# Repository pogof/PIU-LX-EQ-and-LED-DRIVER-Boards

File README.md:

Before you continue reading:
Both boards are relatively simple, both based on AtMega238p
and both running the same code. Both original board types
have the chip unlocked, meaning that with some programmer
or even just Arduino running the Example programmer sketch
you can read the code and flash it to another.

If you have a board that died you can first try to revive it
by flashing code downloaded from a working board. If that doesn't
work, try checking for component failure (caps shorted, ...),
replace the AtMega238p and flash again.

Please be careful, I am not responsible if you accidentally
damage, wipe or owerwrite your working boards!!!

If you are missing a board or want to make more continue reading.

## WHAT IS THIS?

In this archive you will find two KiCad 10 projects + all footprint
and symbol libraries. One project has the main EQ board and the other
the 3 light boards that are chained to the EQ board.

The connections were just traced by eye and multimeter.

The included schematics map out all the components as found on the original
boards. There are links to manufacturers websites of the connectors.

The PCB design should really only be used as a reference. The size
and mounting hole spacing has been checked and is correct. Component
layout is approximately the same as on the original board,
but the passives have whatever footprint I found, same as the dipswitch
and some other components. Basically if you want to make it,
make sure you change the footprints on the board to
what is actually available.

**PLEASE NOTE THAT YOU WILL NEED AT LEAST ONE OF THE ORIGINAL BOARDS
AND AT LEAST AN ARDUINO TO GET THE CODE OFF OF THE ORIGINAL BOARD.
I do not and will not share so i don't get in troubles.
This archive was made just for preservation purposes.**

# Other then the 2pin and 4pin power connectors, the footprint connectors are correct.

For the mini-fit: The footprint I have selected and the actual component I bought are slightly different, where the footprint is slightly rectangular, but the actual component I bought is square. I am not sure if there is different SKUs that differ or if it is straight up different connectors. Will update when I investigate some more.

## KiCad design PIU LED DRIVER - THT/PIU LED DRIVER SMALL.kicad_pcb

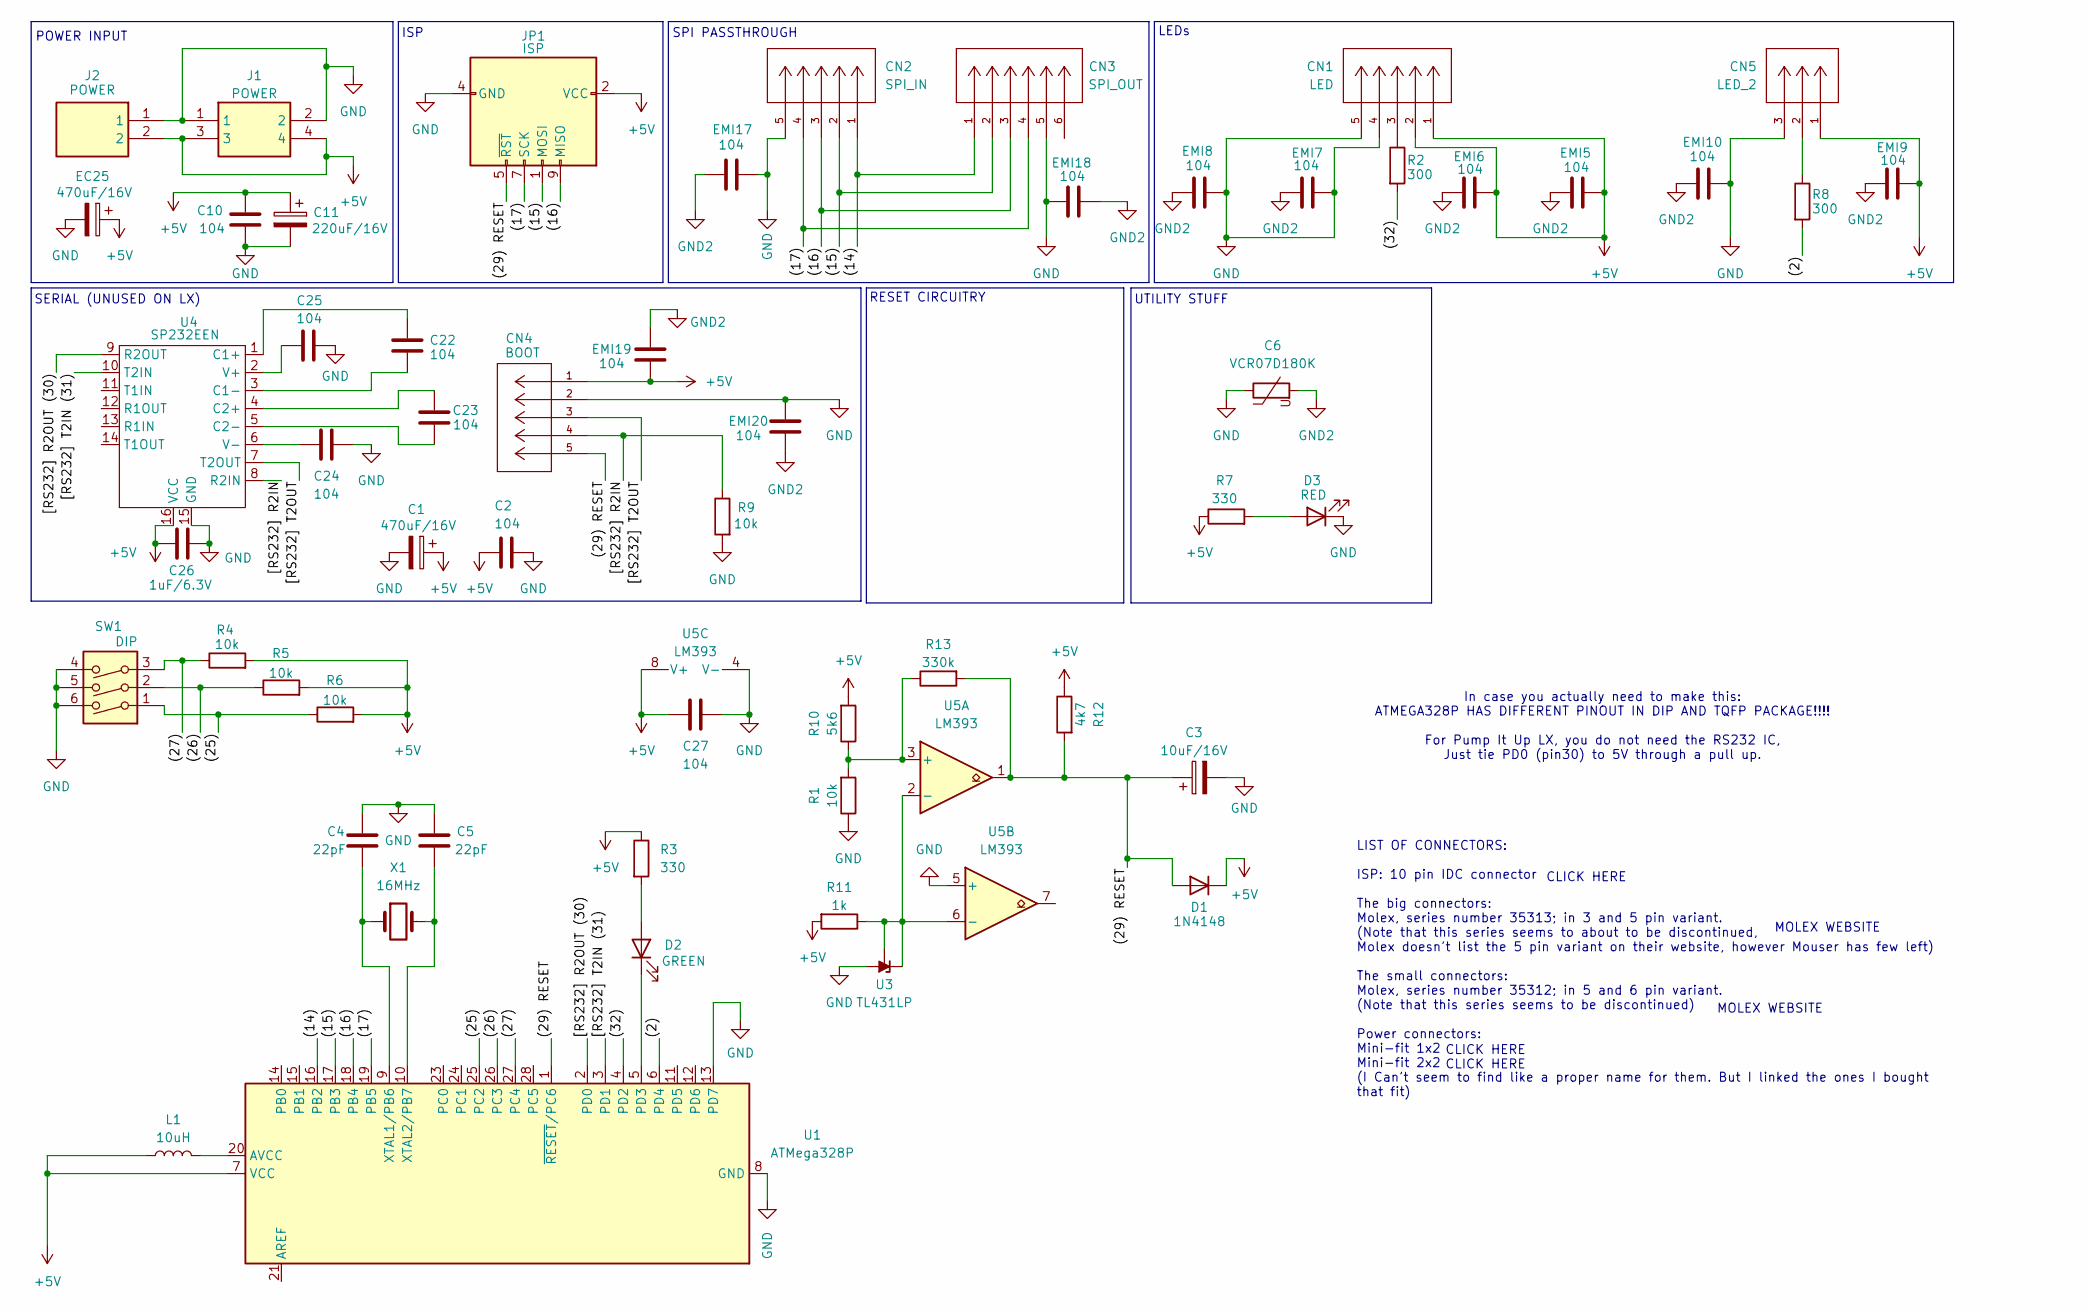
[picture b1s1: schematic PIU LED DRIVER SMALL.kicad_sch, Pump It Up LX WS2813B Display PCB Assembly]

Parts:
C1: 470uF/16V; CP_Radial_D8.0mm_P5.00mm
C2, C10, C22, C23, C24, C25, C27: 104; C_Disc_D6.0mm_W2.5mm_P5.00mm
C3: 10uF/16V; CP_Radial_D4.0mm_P2.00mm
C4, C5: 22pF; C_Disc_D3.8mm_W2.6mm_P2.50mm
C6: VCR07D180K; C_Disc_D6.0mm_W2.5mm_P5.00mm
C11: 220uF/16V; CP_Radial_D6.3mm_P2.50mm
C26: 1uF/6.3V; CP_Radial_D5.0mm_P2.00mm
CN1: LED; 35313-0560; MANUFACTURER_PART_NUMBER 353130560
CN2: SPI_IN; 35312-0560; MANUFACTURER_PART_NUMBER 353120560
CN3: SPI_OUT; 35312-0660; MANUFACTURER_PART_NUMBER 353120660
CN4: BOOT; 35312-0560; MANUFACTURER_PART_NUMBER 353120560
CN5: LED_2; 35313-0360; MANUFACTURER_PART_NUMBER 353130360
D1: 1N4148; D_DO-35_SOD27_P7.62mm_Horizontal
D2: GREEN; LED_D5.0mm
D3: RED; LED_D5.0mm
EC25: 470uF/16V; CP_Radial_D8.0mm_P5.00mm
EMI5, EMI6, EMI7, EMI8, EMI9, EMI10, EMI17, EMI18, EMI19, EMI20: 104; C_Disc_D6.0mm_W2.5mm_P5.00mm
J1: POWER; 39-29-3046; Mouser Part Number 538-39-29-3046
J2: POWER; 39-29-3026; Mouser Part Number 538-39-29-3026
JP1: ISP; IDC-Header_2x05_P2.54mm_Vertical
L1: 10uH; L_Axial_L7.0mm_D3.3mm_P12.70mm_Horizontal_Fastron_MICC
R1, R4, R5, R6, R9: 10k; R_Axial_DIN0207_L6.3mm_D2.5mm_P2.54mm_Vertical
R2: 300; R_Axial_DIN0207_L6.3mm_D2.5mm_P2.54mm_Vertical
R3, R7: 330; R_Axial_DIN0207_L6.3mm_D2.5mm_P2.54mm_Vertical
R8: 300; R_Axial_DIN0207_L6.3mm_D2.5mm_P10.16mm_Horizontal
R10: 5k6; R_Axial_DIN0207_L6.3mm_D2.5mm_P2.54mm_Vertical
R11: 1k; R_Axial_DIN0207_L6.3mm_D2.5mm_P2.54mm_Vertical
R12: 4k7; R_Axial_DIN0207_L6.3mm_D2.5mm_P2.54mm_Vertical
R13: 330k; R_Axial_DIN0207_L6.3mm_D2.5mm_P2.54mm_Vertical
SW1: DIP; SW_DIP_SPSTx03_Slide_6.7x9.18mm_W7.62mm_P2.54mm_LowProfile
U1: ATMega328P; DIP-28_W7.62mm
U3: TL431LP; TO-92L_Inline_Wide
U4: SP232EEN; SO-16_3.9x9.9mm_P1.27mm
U5: LM393; DIP-8_W7.62mm_LongPads
X1: 16MHz; Crystal_HC18-U_Vertical

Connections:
+5V: C1.1, C2.2, C10.1, C11.1, C26.1, C27.2, CN1.1, CN1.2, CN4.1, CN5.1, D1.1 (K), EC25.1, EMI5.2, EMI6.2, EMI9.2, EMI19.1, J1.3, J1.4, J2.2, JP1.2 (VCC), L1.1, R3.1, R4.2, R5.2, R6.2, R7.1, R10.2, R11.2, R12.1, U1.7 (VCC), U4.16 (VCC), U5.8 (V+)
/(2): R8.2, U1.6 (PD4)
/(14): CN2.1, CN3.1, U1.16 (PB2)
/(15): CN2.2, CN3.2, JP1.1 (MOSI), U1.17 (PB3)
/(16): CN2.3, CN3.3, JP1.9 (MISO), U1.18 (PB4)
/(17): CN2.4, CN3.4, JP1.7 (SCK), U1.19 (PB5)
/(25): R6.1, SW1.1, U1.25 (PC2)
/(26): R5.1, SW1.2, U1.26 (PC3)
/(27): R4.1, SW1.3, U1.27 (PC4)
/(29) RESET: C3.1, CN4.5, D1.2 (A), JP1.5 (~RST), R12.2, R13.2, U1.1 (~RESET/PC6), U5.1
/(32): R2.2, U1.4 (PD2)
/[RS232] R2IN: CN4.4, R9.1, U4.8 (R2IN)
/[RS232] R2OUT (30): U1.2 (PD0), U4.9 (R2OUT)
/[RS232] T2IN (31): U1.3 (PD1), U4.10 (T2IN)
/[RS232] T2OUT: CN4.3, U4.7 (T2OUT)
GND: C1.2, C2.1, C3.2, C4.1, C5.1, C6.1, C10.2, C11.2, C24.1, C25.1, C26.2, C27.1, CN1.4, CN1.5, CN2.5, CN3.5, CN4.2, CN5.3, D3.1 (K), EC25.2, EMI7.2, EMI8.2, EMI10.2, EMI17.2, EMI18.1, EMI20.2, J1.1, J1.2, J2.1, JP1.4 (GND), JP1.6 (GND), JP1.8 (GND), JP1.10 (GND), R1.1, R9.2, SW1.4, SW1.5, SW1.6, U1.8 (GND), U1.13 (PD7), U1.22 (GND), U3.2 (A), U4.15 (GND), U5.4 (V-), U5.5 (+)
GND2: C6.2, EMI5.1, EMI6.1, EMI7.1, EMI8.1, EMI9.1, EMI10.1, EMI17.1, EMI18.2, EMI19.2, EMI20.1
unnamed: CN1.3, R2.1
unnamed: CN5.2, R8.1
unnamed: D2.2 (A), R3.2
unnamed: D2.1 (K), U1.5 (PD3)
unnamed: D3.2 (A), R7.2
unnamed: L1.2, U1.20 (AVCC)
unnamed: C4.2, U1.9 (XTAL1/PB6), X1.1
unnamed: C5.2, U1.10 (XTAL2/PB7), X1.2
unnamed: R11.1, U3.1 (REF), U3.3 (K), U5.2 (-), U5.6 (-)
unnamed: C22.2, U4.1 (C1+)
unnamed: C22.1, U4.3 (C1-)
unnamed: C23.1, U4.4 (C2+)
unnamed: C23.2, U4.5 (C2-)
unnamed: C25.2, U4.2 (V+)
unnamed: C24.2, U4.6 (V-)
unnamed: R1.2, R10.1, R13.1, U5.3 (+)

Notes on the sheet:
CLICK HERE
MOLEX WEBSITE
LEDs
UTILITY STUFF
SERIAL (UNUSED ON LX)
SPI PASSTHROUGH
POWER INPUT
In case you actually need to make this: ATMEGA328P HAS DIFFERENT PINOUT IN DIP AND TQFP PACKAGE!!!! For Pump It Up LX, you do not need the RS232 IC, Just tie PD0 (pin30) to 5V through a pull up.
ISP
LIST OF CONNECTORS: ISP: 10 pin IDC connector The big connectors: Molex, series number 35313; in 3 and 5 pin variant. (Note that this series seems to about to be discontinued, Molex doesn't list the 5 pin variant on their website, however Mouser has few left) The small connectors: Molex, series num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
RESET CIRCUITRY

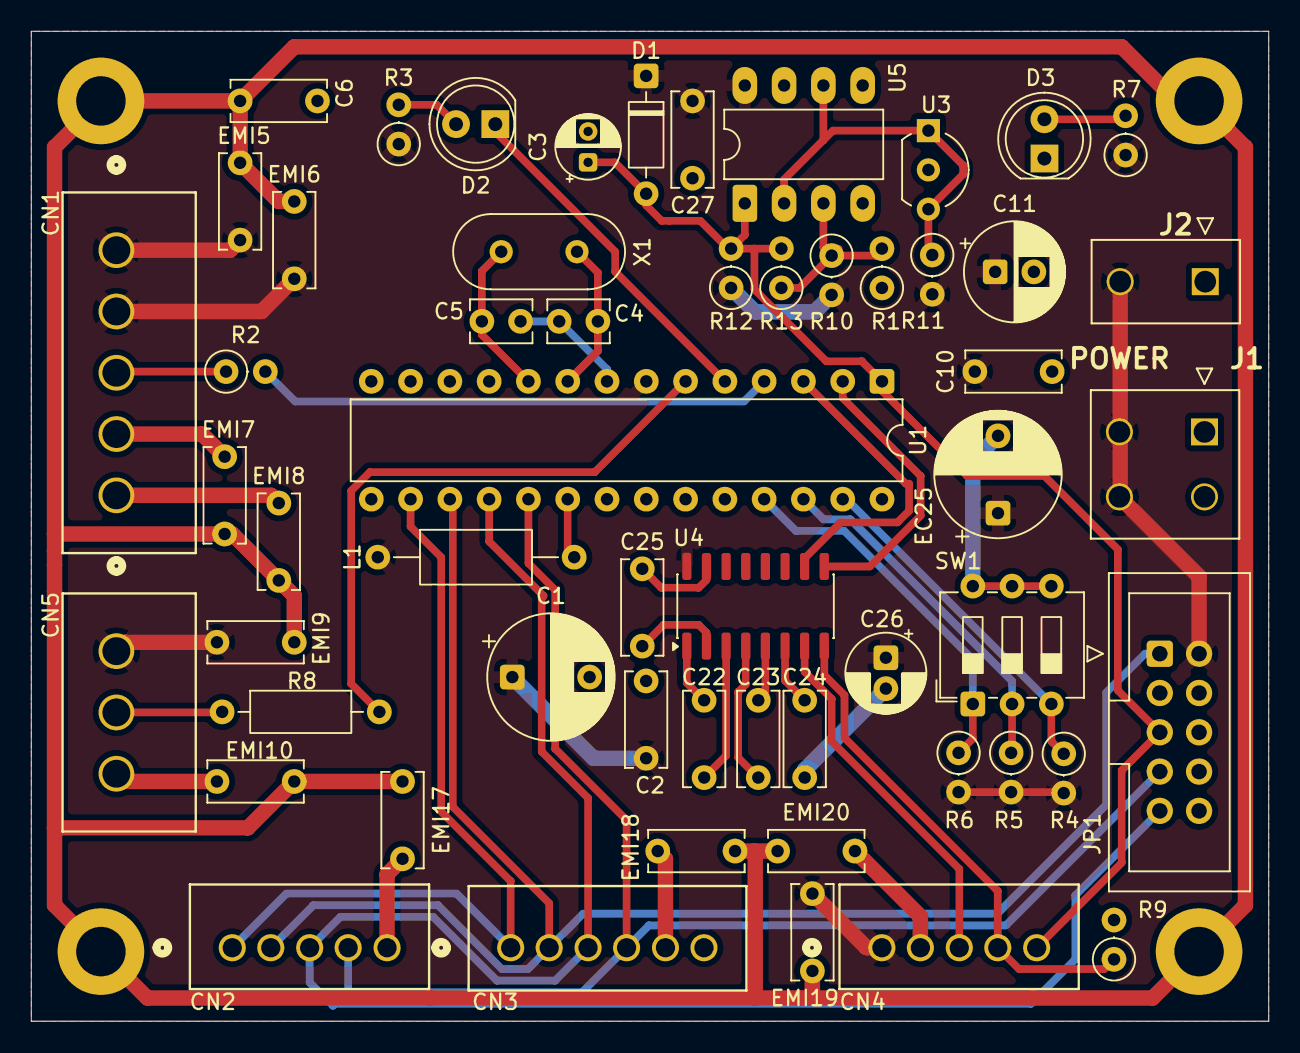
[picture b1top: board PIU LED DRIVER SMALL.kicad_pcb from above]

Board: 2 copper layers, 80.0 x 64.0 mm, 56 parts (0 on the bottom side), 33 nets.

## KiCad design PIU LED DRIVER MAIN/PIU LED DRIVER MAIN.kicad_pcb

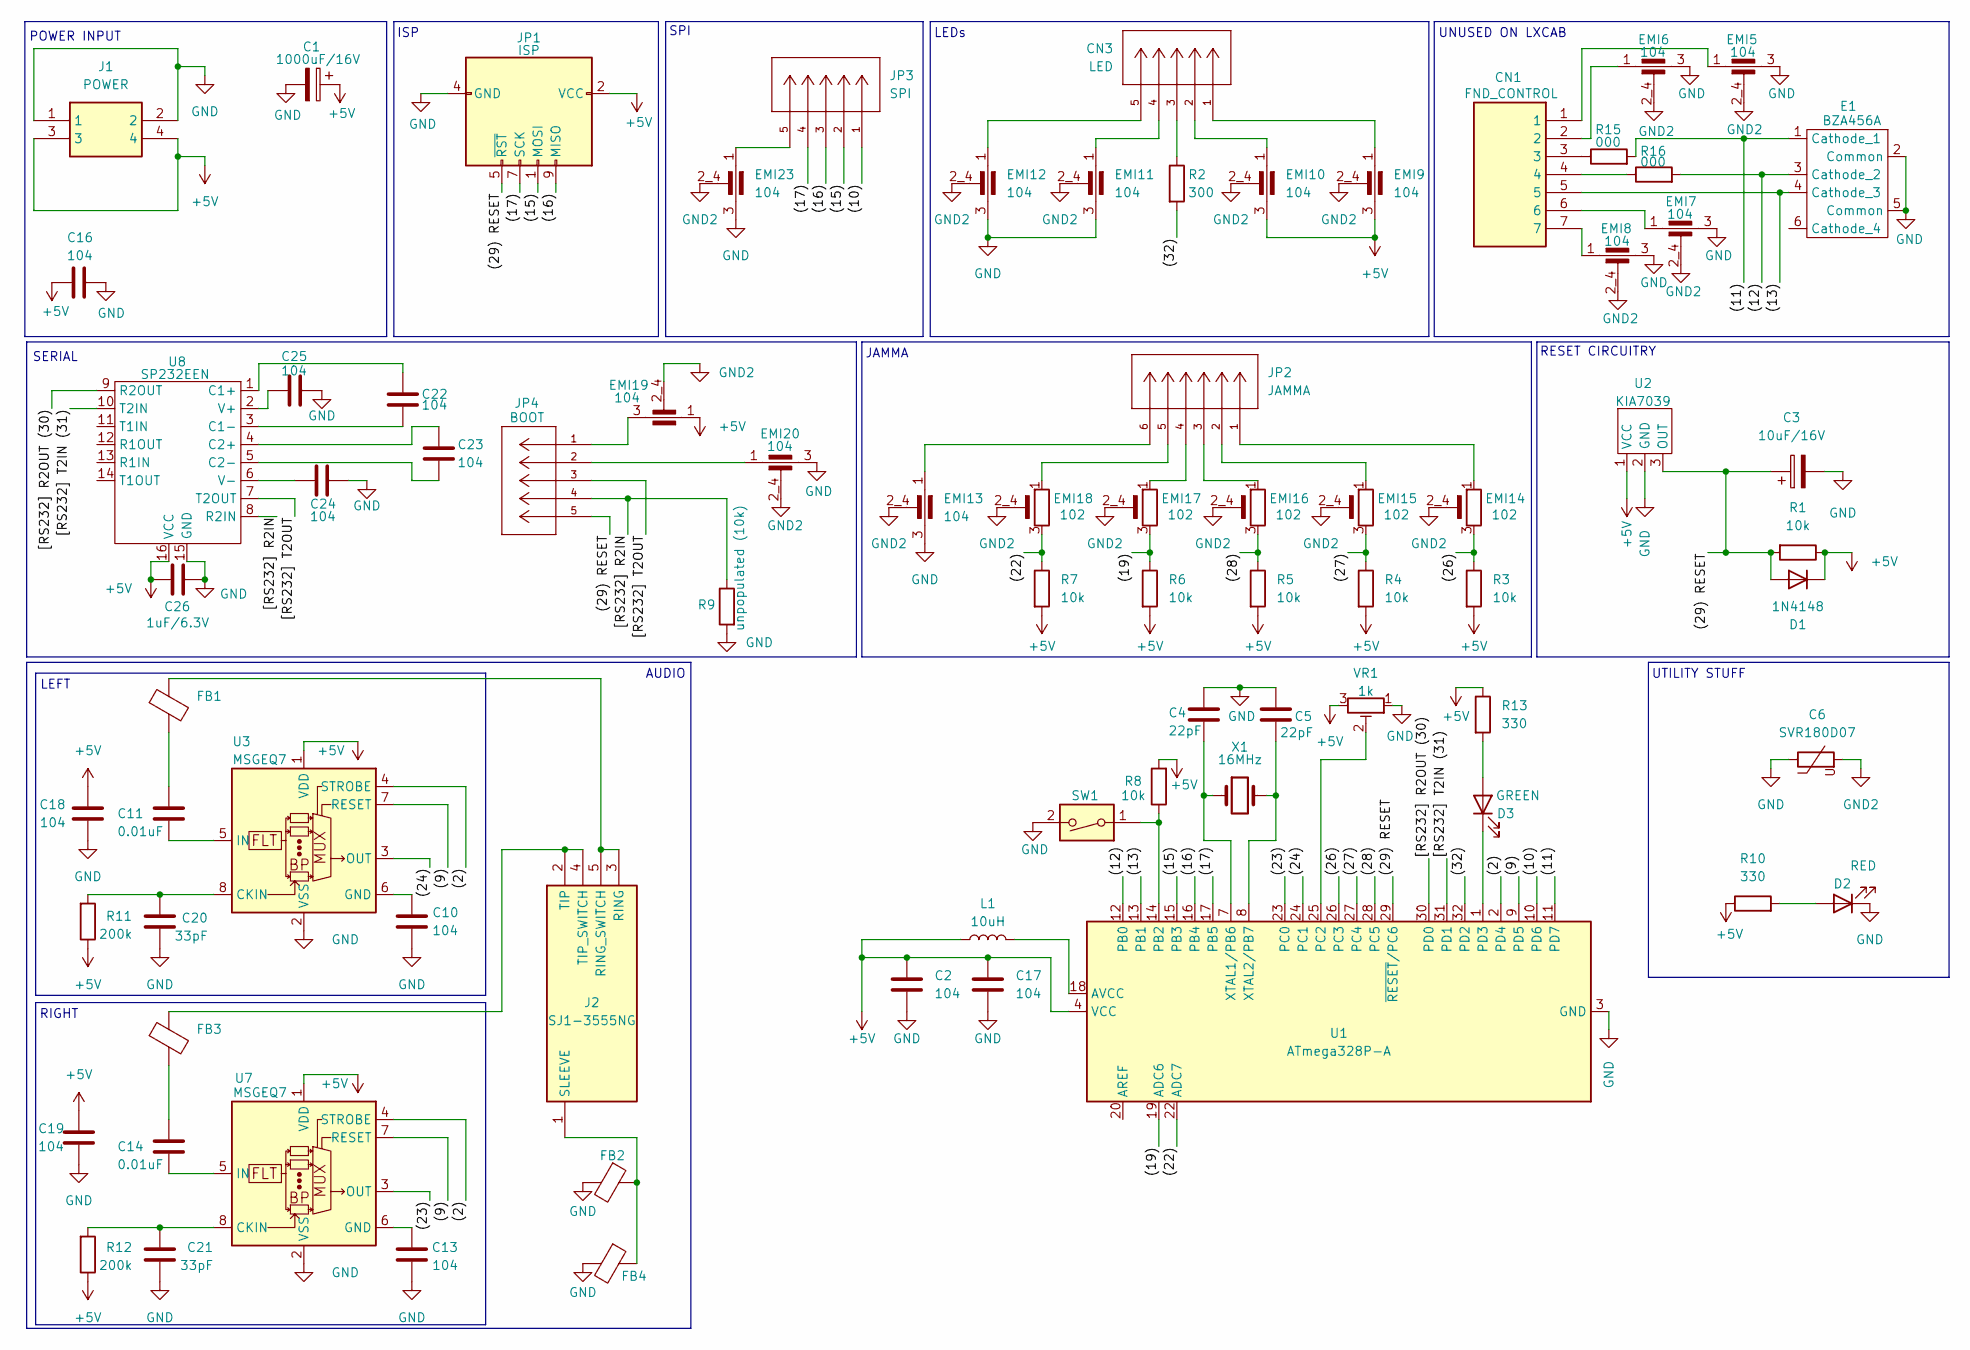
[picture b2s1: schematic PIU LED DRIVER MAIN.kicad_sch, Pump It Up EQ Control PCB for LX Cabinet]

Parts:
C1: 1000uF/16V; CP_Radial_D10.0mm_P5.00mm
C2, C10, C13, C16, C17, C18, C19, C22, C23, C24, C25: 104; L_1206_3216Metric_Pad1.22x1.90mm_HandSolder
C3: 10uF/16V; CP_Elec_4x4.5
C4, C5: 22pF; L_1206_3216Metric_Pad1.22x1.90mm_HandSolder
C6: SVR180D07; Resonator-2Pin_W6.0mm_H3.0mm
C11, C14: 0.01uF; L_1206_3216Metric_Pad1.22x1.90mm_HandSolder
C20, C21: 33pF; L_1206_3216Metric_Pad1.22x1.90mm_HandSolder
C26: 1uF/6.3V; L_1206_3216Metric_Pad1.22x1.90mm_HandSolder
CN1: FND_CONTROL; 35312-0760; Mouser Part Number 538-35312-0760
CN3: LED; 35313-0560; MANUFACTURER_PART_NUMBER 353130560
D1: 1N4148; D_DO-35_SOD27_P7.62mm_Horizontal
D2: RED; L_1206_3216Metric_Pad1.22x1.90mm_HandSolder
D3: GREEN; L_1206_3216Metric_Pad1.22x1.90mm_HandSolder
E1: BZA456A; SOT-457T
EMI5, EMI6, EMI7, EMI8, EMI9, EMI10, EMI11, EMI12, EMI13, EMI19, EMI20, EMI23: 104; FIL_YFF31HC2A104M
EMI14, EMI15, EMI16, EMI17, EMI18: 102; FIL_YFF31HC2A104M
FB1, FB2, FB3, FB4: FerriteBead; L_Axial_L12.0mm_D5.0mm_P15.24mm_Horizontal_Fastron_MISC
J1: POWER; 39-29-3046; Mouser Part Number 538-39-29-3046
J2: SJ1-3555NG; SJ13555NG; Mouser Part Number 490-SJ1-3555NG
JP1: ISP; IDC-Header_2x05_P2.54mm_Vertical
JP2: JAMMA; 35312-0660; MANUFACTURER_PART_NUMBER 353120660
JP3: SPI; 35312-0560; MANUFACTURER_PART_NUMBER 353120560
JP4: BOOT; 35312-0560; MANUFACTURER_PART_NUMBER 353120560
L1: 10uH; L_1206_3216Metric_Pad1.22x1.90mm_HandSolder
R1, R3, R4, R5, R6, R7, R8: 10k; L_1206_3216Metric_Pad1.22x1.90mm_HandSolder
R2: 300; L_1206_3216Metric_Pad1.22x1.90mm_HandSolder
R9: unpopulated (10k); L_1206_3216Metric_Pad1.22x1.90mm_HandSolder
R10, R13: 330; L_1206_3216Metric_Pad1.22x1.90mm_HandSolder
R11, R12: 200k; L_1206_3216Metric_Pad1.22x1.90mm_HandSolder
R15, R16: 000; L_1206_3216Metric_Pad1.22x1.90mm_HandSolder
SW1: DIPSW-1P; SW_DIP_SPSTx01_Slide_6.7x4.1mm_W7.62mm_P2.54mm_LowProfile
U1: ATmega328P-A; TQFP-32_7x7mm_P0.8mm
U2: KIA7039; SOT-89-3_Handsoldering
U3, U7: MSGEQ7; SOIC-8_3.9x4.9mm_P1.27mm
U8: SP232EEN; SO-16_3.9x9.9mm_P1.27mm
VR1: 1k; Potentiometer_Vishay_T73YP_Vertical
X1: 16MHz; Crystal_HC18-U_Vertical

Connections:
+5V: C1.1, C2.1, C16.2, C17.1, C18.1, C19.1, C26.1, D1.1 (K), EMI9.3, EMI10.3, EMI19.1, J1.3, J1.4, JP1.2 (VCC), L1.1, R1.1, R3.2, R4.2, R5.2, R6.2, R7.2, R8.2, R10.1, R11.1, R12.1, R13.1, U1.4 (VCC), U1.6 (VCC), U2.1 (VCC), U3.1 (VDD), U7.1 (VDD), U8.16 (VCC), VR1.3
/PIU LED DRIVER MAIN/(2): U1.2 (PD4), U3.4 (STROBE), U7.4 (STROBE)
/PIU LED DRIVER MAIN/(9): U1.9 (PD5), U3.7 (RESET), U7.7 (RESET)
/PIU LED DRIVER MAIN/(10): JP3.1, U1.10 (PD6)
/PIU LED DRIVER MAIN/(11): E1.1 (Cathode_1), R15.2, U1.11 (PD7)
/PIU LED DRIVER MAIN/(12): E1.3 (Cathode_2), R16.2, U1.12 (PB0)
/PIU LED DRIVER MAIN/(13): CN1.5, E1.4 (Cathode_3), U1.13 (PB1)
/PIU LED DRIVER MAIN/(15): JP1.1 (MOSI), JP3.2, U1.15 (PB3)
/PIU LED DRIVER MAIN/(16): JP1.9 (MISO), JP3.3, U1.16 (PB4)
/PIU LED DRIVER MAIN/(17): JP1.7 (SCK), JP3.4, U1.17 (PB5)
/PIU LED DRIVER MAIN/(19): EMI17.3, R6.1, U1.19 (ADC6)
/PIU LED DRIVER MAIN/(22): EMI18.3, R7.1, U1.22 (ADC7)
/PIU LED DRIVER MAIN/(23): U1.23 (PC0), U7.3 (OUT)
/PIU LED DRIVER MAIN/(24): U1.24 (PC1), U3.3 (OUT)
/PIU LED DRIVER MAIN/(26): EMI14.3, R3.1, U1.26 (PC3)
/PIU LED DRIVER MAIN/(27): EMI15.3, R4.1, U1.27 (PC4)
/PIU LED DRIVER MAIN/(28): EMI16.3, R5.1, U1.28 (PC5)
/PIU LED DRIVER MAIN/(29) RESET: C3.1, D1.2 (A), JP1.5 (~RST), JP4.5, R1.2, U1.29 (~RESET/PC6), U2.3 (OUT)
/PIU LED DRIVER MAIN/(32): R2.2, U1.32 (PD2)
/PIU LED DRIVER MAIN/[RS232] R2IN: JP4.4, R9.1, U8.8 (R2IN)
/PIU LED DRIVER MAIN/[RS232] R2OUT (30): U1.30 (PD0), U8.9 (R2OUT)
/PIU LED DRIVER MAIN/[RS232] T2IN (31): U1.31 (PD1), U8.10 (T2IN)
/PIU LED DRIVER MAIN/[RS232] T2OUT: JP4.3, U8.7 (T2OUT)
GND: C1.2, C2.2, C3.2, C4.1, C5.1, C6.1, C10.1, C13.1, C16.1, C17.2, C18.2, C19.2, C20.1, C21.1, C24.1, C25.1, C26.2, D2.1 (K), E1.2 (Common), E1.5 (Common), EMI5.3, EMI6.3, EMI7.3, EMI8.3, EMI11.3, EMI12.3, EMI13.3, EMI20.3, EMI23.3, FB2.2, FB4.2, J1.1, J1.2, JP1.4 (GND), JP1.6 (GND), JP1.8 (GND), JP1.10 (GND), R9.2, SW1.2, U1.3 (GND), U1.5 (GND), U1.21 (GND), U2.2 (GND), U3.2 (VSS), U7.2 (VSS), U8.15 (GND), VR1.1
GND2: C6.2, EMI5.2_4 (2), EMI6.2_4 (2), EMI7.2_4 (2), EMI8.2_4 (2), EMI9.2_4 (2), EMI10.2_4 (2), EMI11.2_4 (2), EMI12.2_4 (2), EMI13.2_4 (2), EMI14.2_4, EMI15.2_4, EMI16.2_4, EMI17.2_4, EMI18.2_4, EMI19.2_4 (2), EMI20.2_4 (2), EMI23.2_4 (2)
unnamed: C11.1, FB1.2
unnamed: C14.1, FB3.2
unnamed: CN1.1, EMI5.1
unnamed: CN1.2, EMI6.1
unnamed: CN1.3, R15.1
unnamed: CN1.4, R16.1
unnamed: CN1.6, EMI7.1
unnamed: CN1.7, EMI8.1
unnamed: CN3.1, EMI9.1
unnamed: CN3.2, EMI10.1
unnamed: CN3.3, R2.1
unnamed: CN3.4, EMI11.1
unnamed: CN3.5, EMI12.1
unnamed: D2.2 (A), R10.2
unnamed: D3.2 (A), R13.2
unnamed: D3.1 (K), U1.1 (PD3)
unnamed: EMI13.1, JP2.6
unnamed: EMI14.1, JP2.1
unnamed: EMI15.1, JP2.2
unnamed: EMI16.1, JP2.3
unnamed: EMI17.1, JP2.4
unnamed: EMI18.1, JP2.5
unnamed: EMI19.3, JP4.1
unnamed: EMI20.1, JP4.2
unnamed: EMI23.1, JP3.5
unnamed: FB1.1, J2.3 (RING), J2.5 (RING_SWITCH)
unnamed: FB2.1, FB4.1, J2.1 (SLEEVE)
unnamed: FB3.1, J2.2 (TIP), J2.4 (TIP_SWITCH)
unnamed: L1.2, U1.18 (AVCC)
unnamed: R8.1, SW1.1, U1.14 (PB2)
unnamed: U1.25 (PC2), VR1.2
unnamed: C4.2, U1.7 (XTAL1/PB6), X1.1
unnamed: C5.2, U1.8 (XTAL2/PB7), X1.2
unnamed: C20.2, R11.2, U3.8 (CKIN)
unnamed: C10.2, U3.6 (GND)
unnamed: C11.2, U3.5 (IN)
unnamed: C21.2, R12.2, U7.8 (CKIN)
unnamed: C13.2, U7.6 (GND)
unnamed: C14.2, U7.5 (IN)
unnamed: C22.2, U8.1 (C1+)
unnamed: C22.1, U8.3 (C1-)
unnamed: C23.1, U8.4 (C2+)
unnamed: C23.2, U8.5 (C2-)
unnamed: C25.2, U8.2 (V+)
unnamed: C24.2, U8.6 (V-)

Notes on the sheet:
POWER INPUT
RESET CIRCUITRY
UNUSED ON LXCAB
LEDs
UTILITY STUFF
LEFT
SPI
SERIAL
JAMMA
RIGHT
ISP
AUDIO

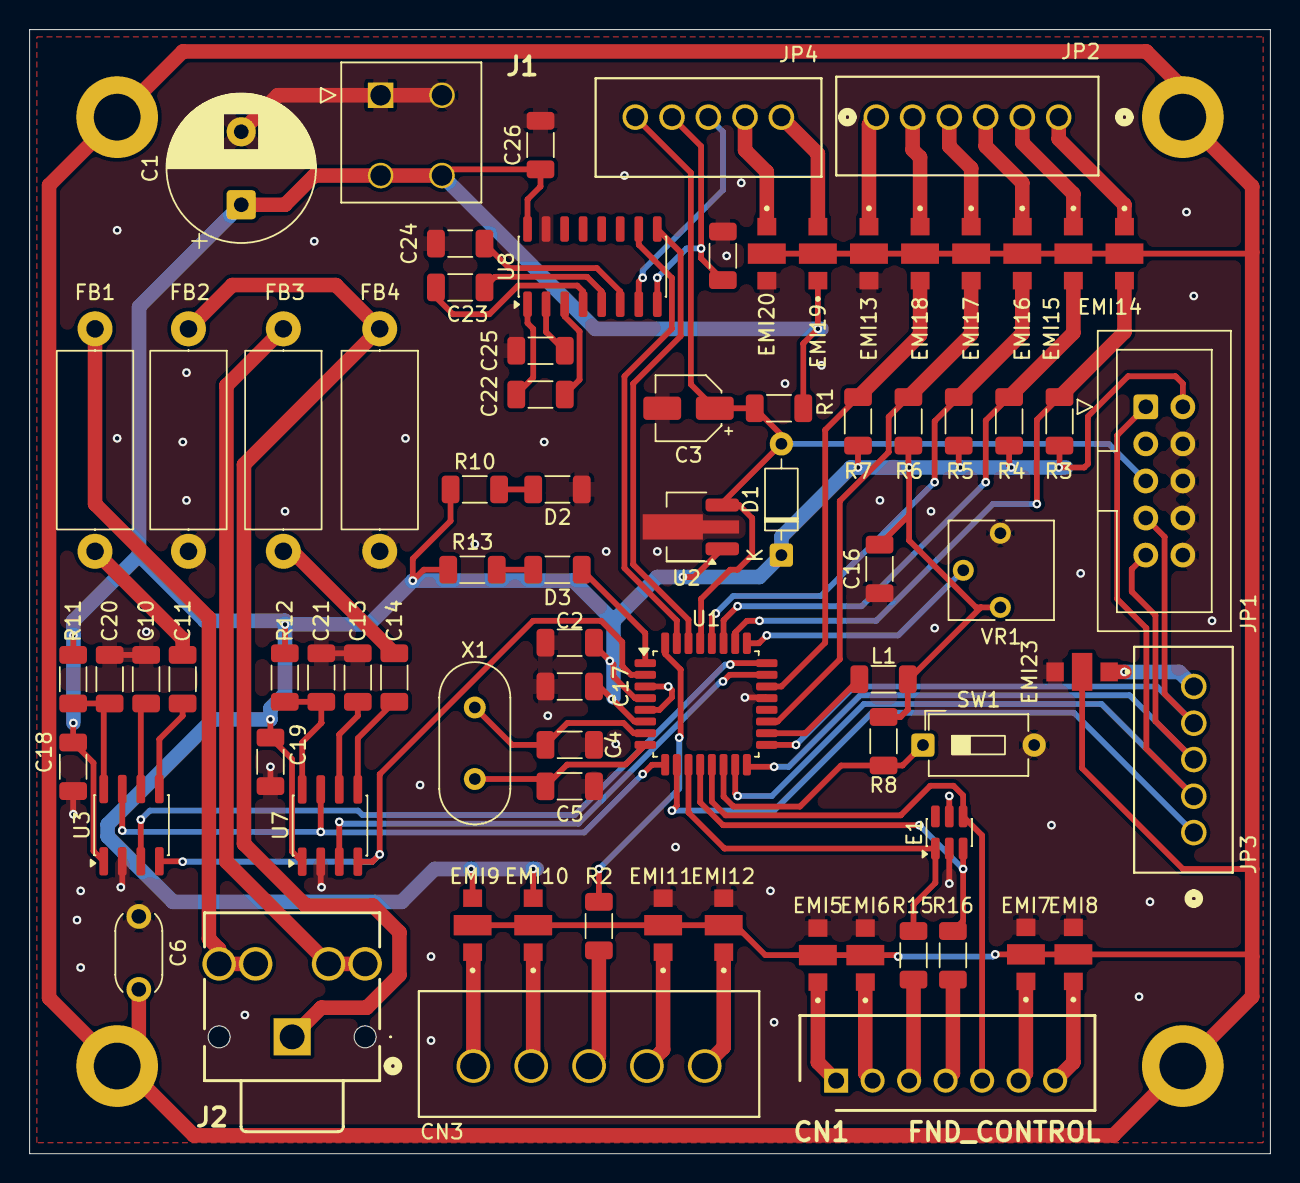
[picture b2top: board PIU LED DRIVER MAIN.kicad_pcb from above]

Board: 2 copper layers, 85.0 x 77.0 mm, 78 parts (0 on the bottom side), 70 nets.
